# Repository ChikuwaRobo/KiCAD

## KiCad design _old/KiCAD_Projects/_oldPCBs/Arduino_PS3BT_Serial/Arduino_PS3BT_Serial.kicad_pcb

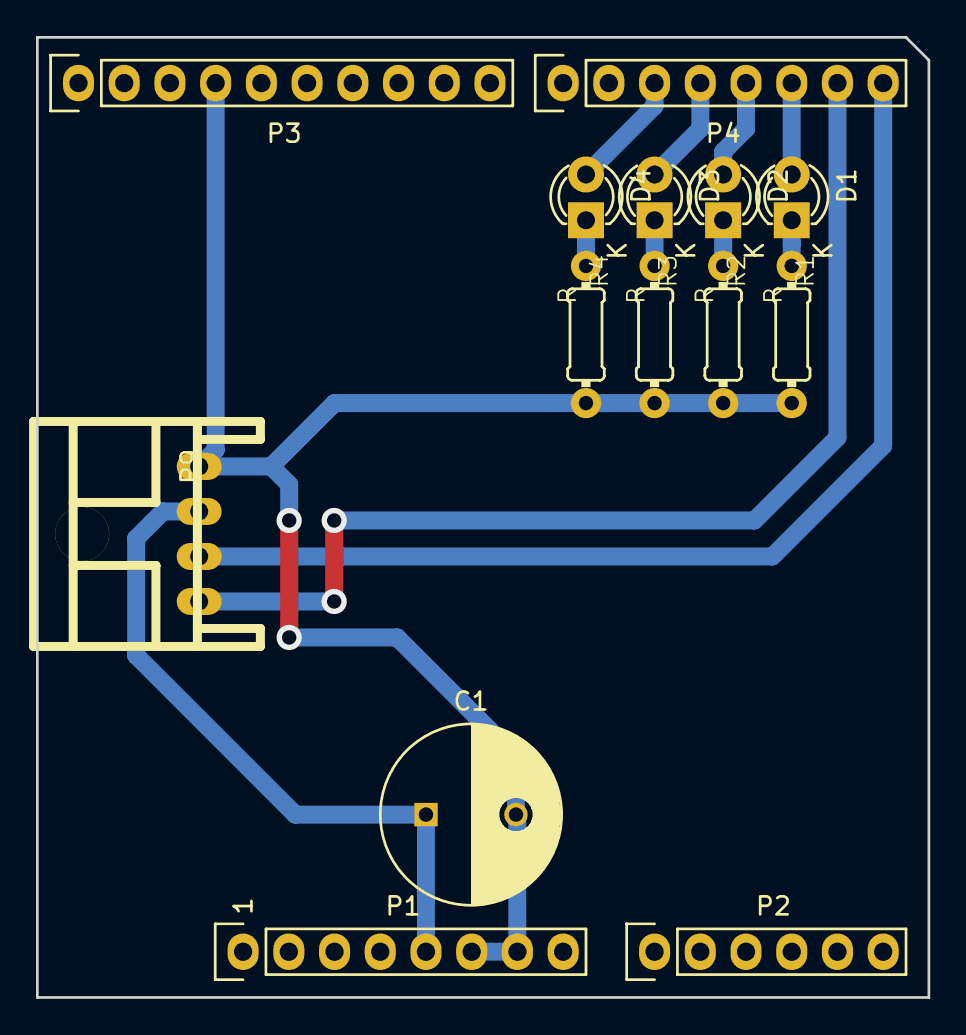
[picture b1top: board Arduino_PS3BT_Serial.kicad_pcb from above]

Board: 2 copper layers, 49.5 x 53.3 mm, 14 parts (0 on the bottom side), 14 nets.

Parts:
C1: 100u; C_Radial_D10_L20_P5
D1, D2, D3, D4: LED; LED-3MM
P1: Power; Socket_Strip_Arduino_1x08
P2: Analog; Socket_Strip_Arduino_1x06
P3: Digital; Socket_Strip_Arduino_1x10
P4: Digital; Socket_Strip_Arduino_1x08
P9: CONN_01X04; XA_4LC
R1, R2, R3, R4: R; 0204_2f7

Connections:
+5V: C1.1, P1.5, P9.2
/0(Rx): P4.8, P9.3
/1(Tx): P4.7, P9.4
/2: D1.2, P4.6
/3(**): D2.2, P4.5
/4: D3.2, P4.4
/5(**): D4.2, P4.3
/A4(SDA): P2.5, P3.2
/A5(SCL): P2.6, P3.1
GND: C1.2, P1.6, P1.7, P3.4, P9.1, R1.2, R2.2, R3.2, R4.2
unnamed: D1.1, R1.1
unnamed: D2.1, R2.1
unnamed: D3.1, R3.1
unnamed: D4.1, R4.1

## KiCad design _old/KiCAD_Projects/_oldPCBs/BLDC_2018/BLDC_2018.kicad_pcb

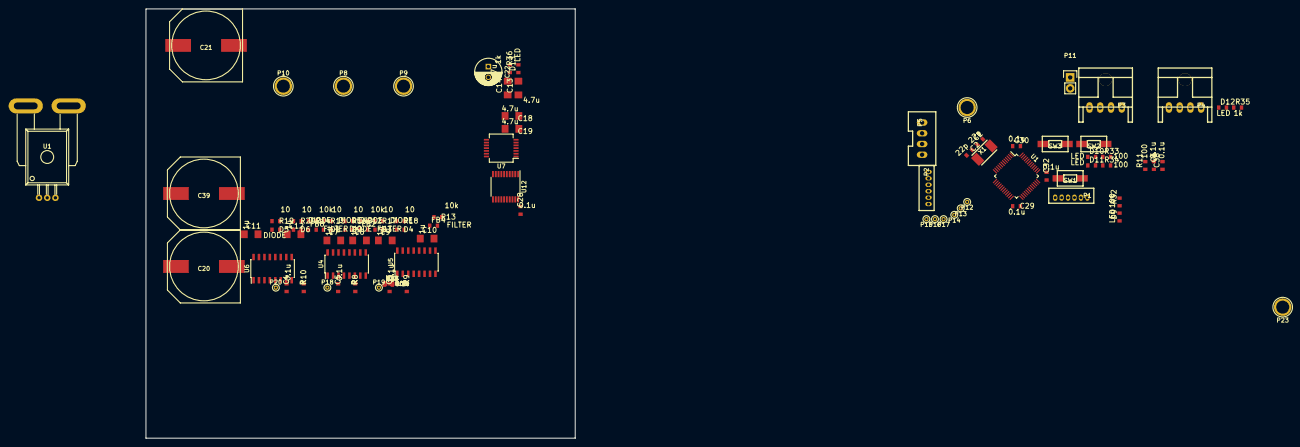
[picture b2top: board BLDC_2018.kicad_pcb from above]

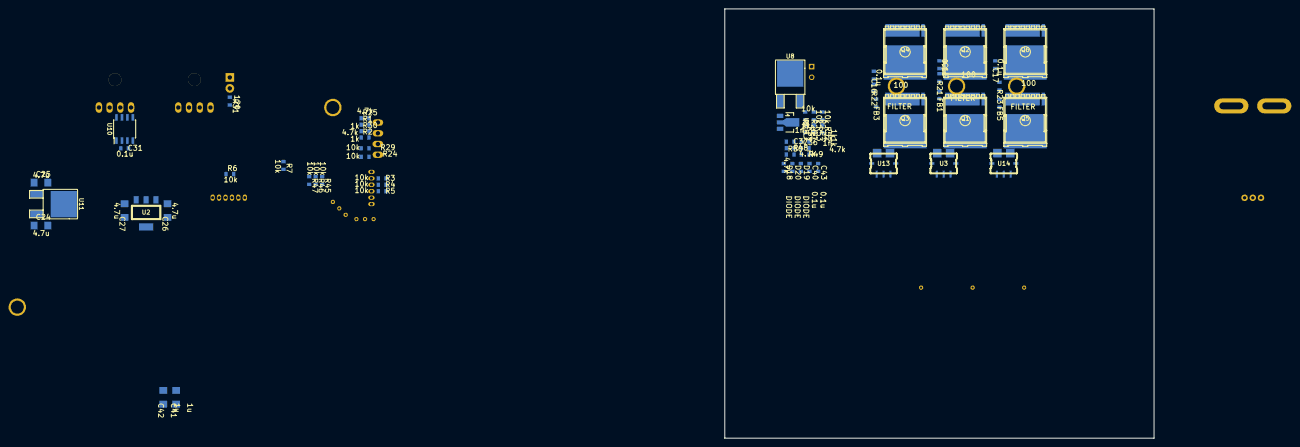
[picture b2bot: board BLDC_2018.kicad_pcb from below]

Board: 2 copper layers, 100.0 x 100.0 mm, 157 parts (62 on the bottom side), 97 nets, no tracks yet.

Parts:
C1, C2: 22p; C1608_WP
C3, C4, C5, C6, C15, C16, C17, C23, C28, C29, C30, C31, C32, C33, C34, C38, C40, C43, C44, C45: 0.1u; C1608_WP
C7, C8, C9, C10, C11, C12, C41, C42: 1u; C3216
C13, C14, C18, C19, C24, C25, C26, C27: 4.7u; C3216
C20, C21, C39: 470u; c_elec_16x17
C22: 100u; C_Radial_D6.3_L11.2_P2.5
C35, C36, C37: 1n; C1608_WP
D1, D2, D3, D4, D5, D6, D18, D19, D20: DIODE; C1608_WP
D9, D10, D11, D12, D13: LED; C1608_WP
FB1, FB2, FB3, FB4, FB5, FB6: FILTER; C1608_WP
P1, P2: CONN_01X06; ZH_6T
P3, P4: CONN_01X04; XA_4LC
P5: CONN_01X04; XA_4T
P6, P8, P9, P10, P23: CONN_01X01; 1pin
P11: CONN_01X02; Pin_Header_Straight_1x02
P12, P13, P14, P15, P16, P17, P18, P19, P20: CONN_01X01; PINTST
Q1, Q2, Q3, Q4, Q5, Q6: MOSFET_N; HSOF-8-1
R1, R2, R35, R36, R52, R53, R54: 1k; C1608_WP
R3, R4, R5, R6, R7, R12, R13, R14, R24, R26, R27, R28, R29, R45, R46, R47: 10k; C1608_WP
R8, R9, R10: R; C1608_WP
R11, R21, R22, R23, R32, R33, R34, R37, R38: 100; C1608_WP
R15, R16, R17, R18, R19, R20: 10; C1608_WP
R25, R30, R48, R49, R50: 4.7k; C1608_WP
R31: 120; C1608_WP
SW1, SW2, SW3: SW_PUSH; RP_SMD_Button
U1: STM32F103_48; LQFP-48_7x7mm_Pitch0.5mm
U1#2: ACS758; ACS785xCB
U2: NCP1117ST33T3G; SOT-223_reg
U3, U13, U14: ACS758; ACS78x
U4, U5, U6: SI8234; SOIC-16_3.9x9.9mm_Pitch1.27mm
U7: LM324; SSOP-14_5.3x6.2mm_Pitch0.65mm
U8: LM7812ACT; TO-252-2Lead
U9: LM7805CT; SOT89-3_Housing
U10: MAX3051; SOIC-8_3.9x4.9mm_Pitch1.27mm
U11: LM7805CT; TO-252-2Lead
U12: ADUM7640; TSSOP-20_4.4x6.5mm_Pitch0.65mm
X1: CRYSTAL; ABM3_2pads

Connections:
+3.3V: C3.1, C4.1, C5.1, C6.1, C23.1, C26.1, C28.1, C29.1, C30.1, C31.1, C32.1, C33.1, C38.1, D9.1, P1.2, R6.1, U1.1, U1.9, U1.24, U1.36, U1.48, U2.2, U4.3, U4.8, U5.3, U5.8, U6.3, U6.8, U10.3, U12.14, U12.20
+5V: C24.1, C27.1, P2.6, P5.2, R1.1, R2.1, R3.1, R4.1, R5.1, U2.3, U11.3
+12V: C25.1, D12.1, P3.2, P4.2, U11.1
+BATT: C15.1, C16.2, C17.2, C20.1, C21.1, C39.1, C41.1, C42.1, P6.1, U3.5, U7.4, U13.5, U14.5
/BOOT0: R7.1, U1.44
/CAN_H: P3.3, P4.3, R31.2, U10.7
/CAN_L: P3.4, P4.4, P11.1, U10.6
/CAN_RX: U1.32, U10.4
/CAN_TX: U1.33, U10.1
/COMP_U: P15.1, U1.16, U12.18
/COMP_V: P16.1, U1.17, U12.17
/COMP_W: P17.1, U1.18, U12.16
/ENC_A: P5.3, R2.2, R30.2
/ENC_B: P5.4, R1.2, R25.2
/EN_U: R47.2, U1.15, U6.5
/EN_V: R46.2, U1.14, U4.5
/EN_W: R45.2, U1.13, U5.5
/GD_12V: C14.1, C18.1, D13.1, R15.1, R16.1, R17.1, R18.1, R19.1, R20.1, U8.3, U9.1
/HALL_0: P2.2, P12.1, R3.2, U1.19
/HALL_1: P2.3, P13.1, R4.2, U1.20
/HALL_2: P2.4, P14.1, R5.2, U1.21
/I_SENSE_U: C34.2, C44.2, C45.2, R11.2, R37.2, R38.2
/LED_A: D10.1, U1.42
/LED_B: D11.1, U1.41
/NRST: R6.2, SW1.2, U1.7
/OUT_CENTER: C35.1, C36.1, C37.1, C40.1, R26.2, R27.2, R28.2, U7.2, U7.9, U7.13
/OUT_U: C11.2, P10.1, Q5.S, Q6.D, R23.1, R28.1, R54.1, U6.14
/OUT_V: C7.2, P8.1, Q1.S, Q2.D, R21.1, R26.1, R53.1, U4.14
/OUT_W: C9.2, P9.1, Q3.S, Q4.D, R22.1, R27.1, R52.1, U5.14
/PWM_U: P20.1, U1.28, U6.1
/PWM_V: P18.1, U1.27, U4.1
/PWM_W: P19.1, U1.26, U5.1
/PW_5V: C19.1, C43.1, D18.1, D19.1, D20.1, U9.3, U12.1, U12.7
/PW_PW: C13.1, C22.1, U8.1
/SW1: SW2.2, U1.45
/SW2: SW3.2, U1.46
/SWCLK: P1.3, U1.37
/SWDIO: P1.4, U1.34
/USART_RX: P1.6, U1.31
/USART_TX: P1.5, U1.30
GND: C1.1, C2.1, C3.2, C4.2, C5.2, C6.2, C23.2, C24.2, C25.2, C26.2, C27.2, C28.2, C29.2, C30.2, C31.2, C32.2, C33.2, C34.1, C38.2, C44.1, C45.1, P1.1, P2.1, P3.1, P4.1, P5.1, R7.2, R8.2, R9.2, R10.2, R24.1, R29.1, R32.2, R33.2, R34.2, R35.2, R45.1, R46.1, R47.1, SW1.1, SW2.1, SW3.1, U1.8, U1.23, U1.35, U1.47, U2.1, U4.4, U5.4, U6.4, U10.2, U10.5, U10.8, U11.2, U12.11, U12.19
GNDPWR: C8.2, C10.2, C12.2, C13.2, C14.2, C18.2, C19.2, C20.2, C21.2, C22.2, C39.2, C40.2, C41.2, C42.2, C43.2, P23.1, Q2.S, Q4.S, Q6.S, R12.1, R13.1, R14.1, R36.2, U4.9, U5.9, U6.9, U7.11, U8.2, U9.2, U12.2, U12.10
unnamed: C1.2, U1.5, X1.1
unnamed: C2.2, U1.6, X1.2
unnamed: C7.1, D1.1, U4.16
unnamed: C8.1, D2.1, U4.11
unnamed: C9.1, D3.1, U5.16
unnamed: C10.1, D4.1, U5.11
unnamed: C11.1, D5.1, U6.16
unnamed: C12.1, D6.1, U6.11
unnamed: C15.2, R21.2
unnamed: C16.1, R22.2
unnamed: C17.1, R23.2
unnamed: C35.2, R54.2, U7.10
unnamed: C36.2, R52.2, U7.12
unnamed: C37.2, R53.2, U7.3
unnamed: D1.2, R15.2
unnamed: D2.2, R16.2
unnamed: D3.2, R17.2
unnamed: D4.2, R18.2
unnamed: D5.2, R19.2
unnamed: D6.2, R20.2
unnamed: D9.2, R32.1
unnamed: D10.2, R33.1
unnamed: D11.2, R34.1
unnamed: D12.2, R35.1
unnamed: D13.2, R36.1
unnamed: D18.2, R48.2, U12.3
unnamed: D19.2, R49.2, U12.5
unnamed: D20.2, R50.2, U12.4
unnamed: FB1.1, U4.15
unnamed: FB1.2, Q1.G
unnamed: FB2.1, R12.2, U4.10
unnamed: FB2.2, Q2.G
unnamed: FB3.1, U5.15
unnamed: FB3.2, Q3.G
unnamed: FB4.1, R13.2, U5.10
unnamed: FB4.2, Q4.G
unnamed: FB5.1, U6.15
unnamed: FB5.2, Q5.G
unnamed: FB6.1, R14.2, U6.10
unnamed: FB6.2, Q6.G
unnamed: P11.2, R31.1
unnamed: Q1.D, U3.4
unnamed: Q3.D, U13.4
unnamed: Q5.D, U14.4
unnamed: R8.1, U4.6
unnamed: R9.1, U5.6
unnamed: R10.1, U6.6
unnamed: R11.1, U3.3
unnamed: R24.2, R25.1, U1.11
unnamed: R29.2, R30.1, U1.10
unnamed: R37.1, U13.3
unnamed: R38.1, U14.3
unnamed: R48.1, U7.8
unnamed: R49.1, U7.14
unnamed: R50.1, U7.1

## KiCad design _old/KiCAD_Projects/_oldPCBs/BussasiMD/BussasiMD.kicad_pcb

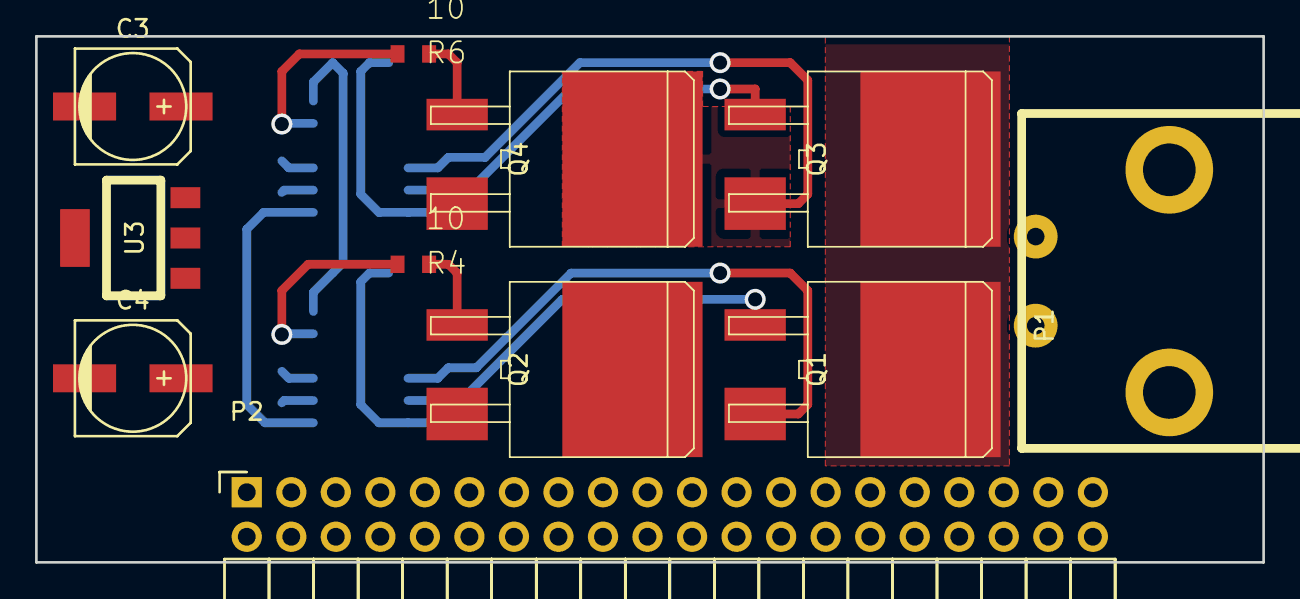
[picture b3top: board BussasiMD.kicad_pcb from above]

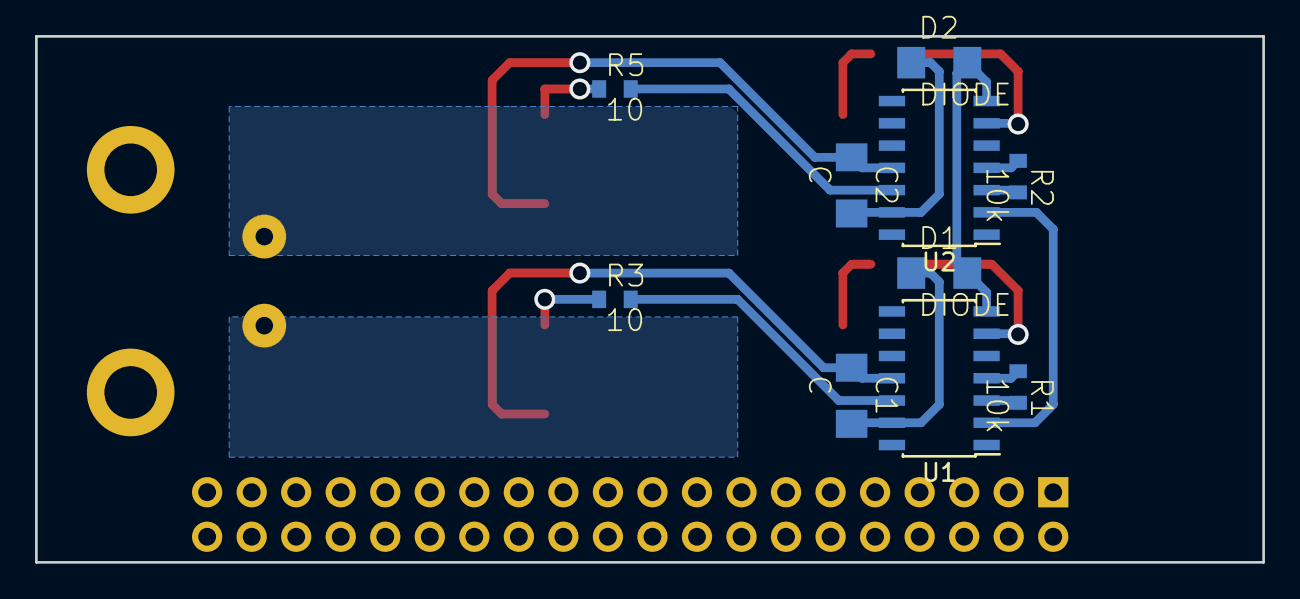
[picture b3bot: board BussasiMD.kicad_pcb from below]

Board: 2 copper layers, 70.0 x 30.0 mm, 21 parts (10 on the bottom side), 21 nets.

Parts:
C1, C2: C; C3216
C3, C4: 100u; c_elec_6.3x4.5
D1, D2: DIODE; C3216
P1: CONN_01X02; D-3200S_2L
P2: CONN_02X20; Socket_Strip_Angled_2x20
Q1, Q2, Q3, Q4: MOSFET_N; D2-PAK_compact
R1, R2: 10k; C1608_WP
R3, R4, R5, R6: 10; C1608_WP
U1, U2: FAN7393; SOIC-14_3.9x8.7mm_Pitch1.27mm
U3: LM7812ACT; SOT-223_reg

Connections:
+12V: C4.1, D1.2, D2.2, U1.7, U2.7, U3.3
+BATT: C3.1, P2.23, P2.24, P2.25, P2.26, P2.27, P2.28, P2.29, P2.30, P2.31, P2.32, P2.33, P2.34, P2.35, P2.36, P2.37, P2.38, P2.39, P2.40, Q1.D, Q3.D, U3.1
/EN: P2.3, U1.2, U2.2
/OUT_A: C1.1, P1.1, Q1.S, Q2.D, U1.11
/OUT_B: C2.1, P1.2, Q3.S, Q4.D, U2.11
/PWM_A: P2.4, U1.1
/PWM_B: P2.2, U2.1
GND: C3.2, C4.2, P2.1, R1.2, R2.2, U1.3, U2.3, U3.2
GNDPWR: P2.5, P2.6, P2.7, P2.8, P2.9, P2.10, P2.11, P2.12, P2.13, P2.14, P2.15, P2.16, P2.17, P2.18, P2.19, P2.20, P2.21, P2.22, Q2.S, Q4.S, U1.5, U2.5
unnamed: C1.2, D1.1, U1.13
unnamed: C2.2, D2.1, U2.13
unnamed: Q1.G, R3.1
unnamed: Q2.G, R4.1
unnamed: Q3.G, R5.1
unnamed: Q4.G, R6.1
unnamed: R1.1, U1.4
unnamed: R2.1, U2.4
unnamed: R3.2, U1.12
unnamed: R4.2, U1.6
unnamed: R5.2, U2.12
unnamed: R6.2, U2.6

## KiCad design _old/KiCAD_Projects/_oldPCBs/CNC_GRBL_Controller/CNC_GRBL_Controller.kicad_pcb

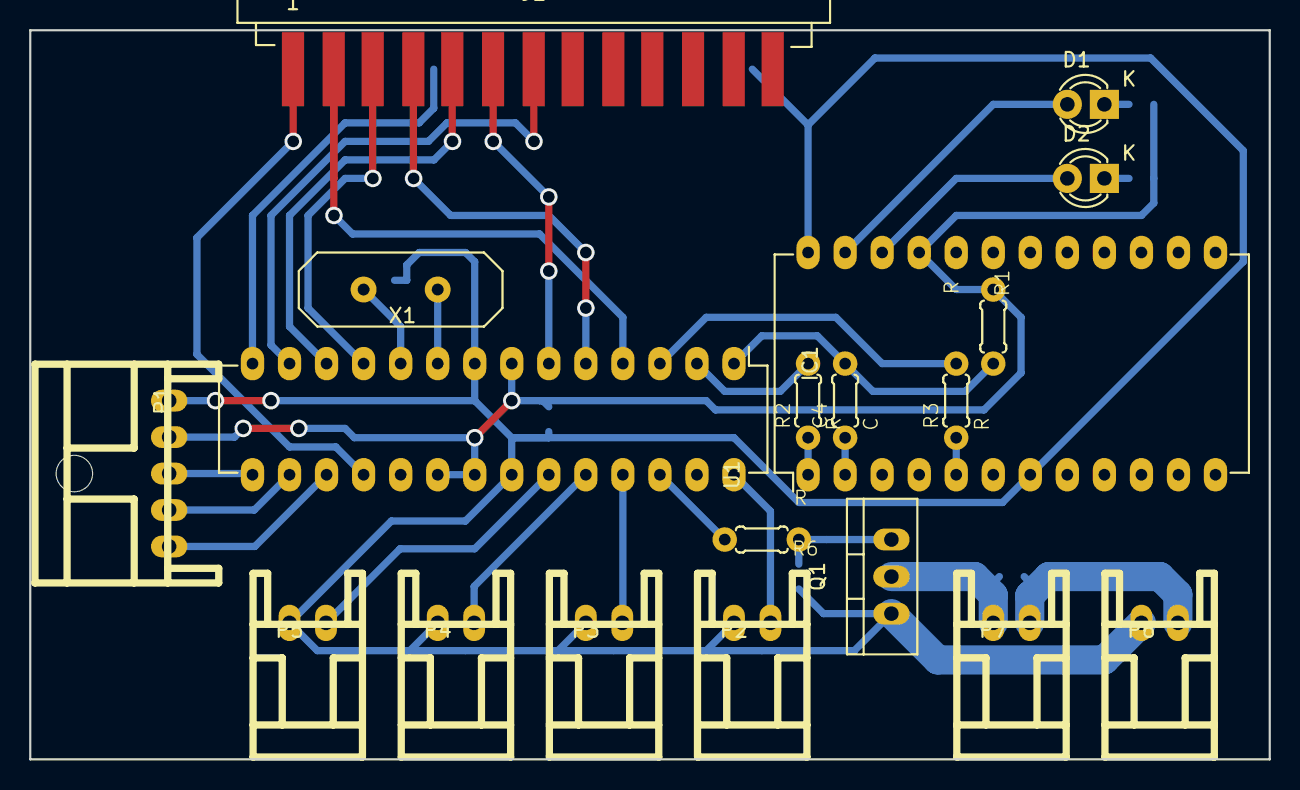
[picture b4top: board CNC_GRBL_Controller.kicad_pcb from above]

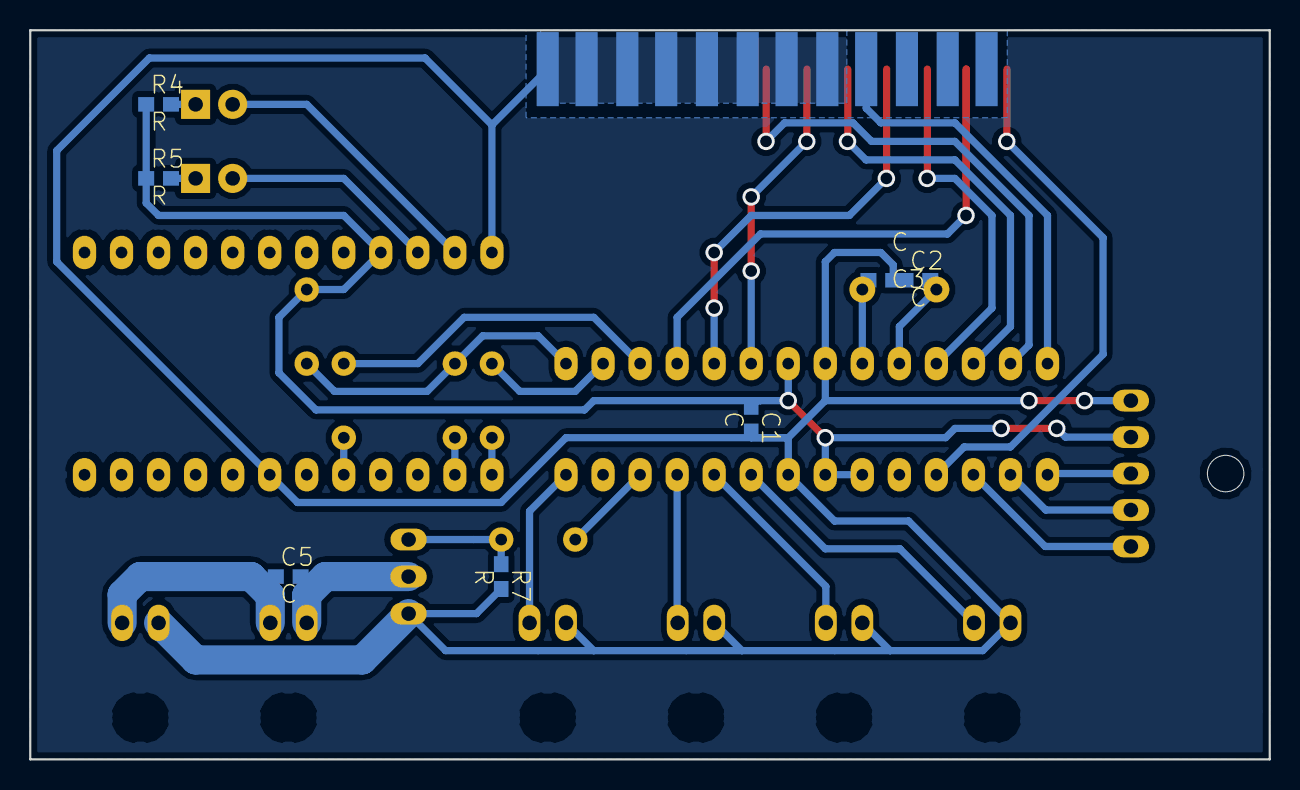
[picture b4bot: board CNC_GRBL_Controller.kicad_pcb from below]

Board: 2 copper layers, 85.0 x 50.0 mm, 26 parts (7 on the bottom side), 33 nets.

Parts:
C1, C2, C3, C5: C; C1608
C4: C; 0204_2f5
D1, D2: LED; LED-3MM
IC1: ATMEGA328-P; DIP-28_W7.62mm_LongPads
J1: DB25; DB25F_CI
P1: CONN_01X05; XA_5L
P2, P3, P4, P5, P6, P7: CONN_01X02; XA_2L
Q1: MOSFET_N; TO-220_Neutral123_Vertical
R1, R2, R3, R6: R; 0204_2f5
R4, R5, R7: R; C1608
U1: AE-UM232R; DIP-24_W15.24mm_LongPads
X1: CRYSTAL; HC-18UV

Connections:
+5V: C1.1, IC1.7, IC1.20, IC1.21, P1.2, R1.1, R4.1, R5.1, U1.21
+12V: C5.1, P6.2, P7.2
/Arduino_RESET: C4.2, IC1.1, R1.2
/Arduino_RX: IC1.2, R2.2
/Arduino_TX: IC1.3, R3.2
/Coolant_EN: IC1.26, R6.2
/Cycle_Stat: IC1.25, P3.2
/Feed_Hold: IC1.24, P4.2
/Limit_X: IC1.15, P1.3
/Limit_Y: IC1.16, P1.4
/Limit_Z: IC1.17, P1.5
/Probe: IC1.28, P2.2
/Reset/Abort: IC1.23, P5.2
/Spindle_EN: IC1.18, J1.1
/Stepper_~EN: IC1.14, J1.17
/X_Dir: IC1.11, J1.3
/X_Step: IC1.4, J1.2
/Y_Dir: IC1.12, J1.5
/Y_Step: IC1.5, J1.4
/Z_Dir: IC1.13, J1.7
/Z_Step: IC1.6, J1.6
GND: C1.2, C2.1, C3.1, IC1.8, IC1.22, J1.18, J1.19, J1.20, J1.21, J1.22, J1.23, J1.24, J1.25, P1.1, P2.1, P3.1, P4.1, P5.1, P6.1, Q1.S, R7.2, U1.7, U1.24
unnamed: C2.2, IC1.10, X1.2
unnamed: C3.2, IC1.9, X1.1
unnamed: C4.1, U1.2
unnamed: C5.2, P7.1, Q1.D
unnamed: D1.1, R4.2
unnamed: D1.2, U1.23
unnamed: D2.1, R5.2
unnamed: D2.2, U1.22
unnamed: Q1.G, R6.1, R7.1
unnamed: R2.1, U1.1
unnamed: R3.1, U1.5

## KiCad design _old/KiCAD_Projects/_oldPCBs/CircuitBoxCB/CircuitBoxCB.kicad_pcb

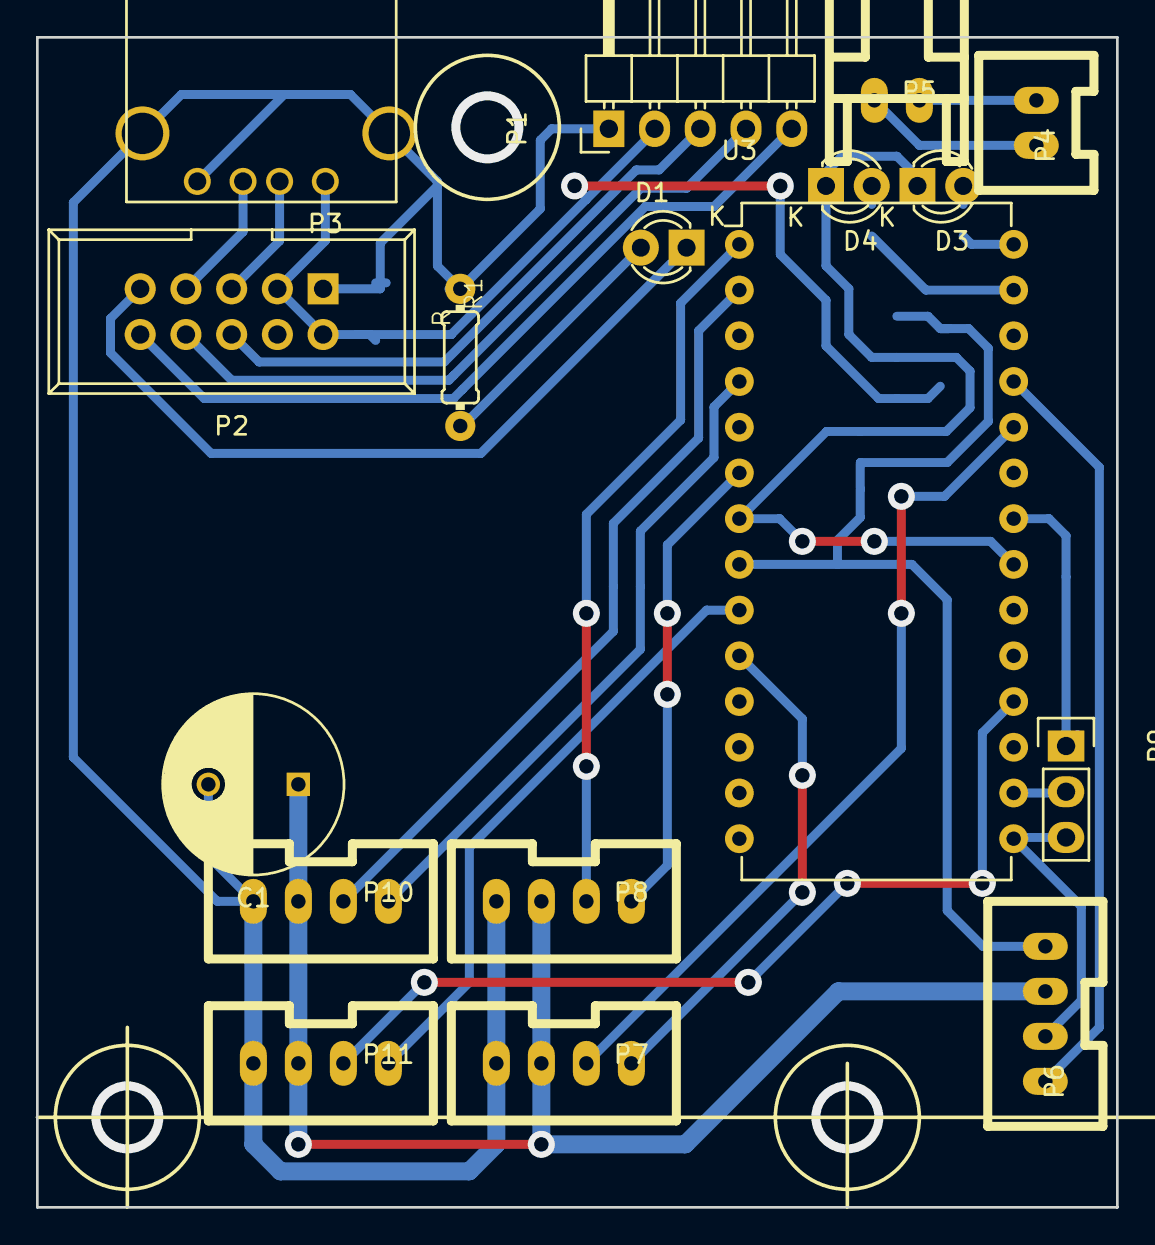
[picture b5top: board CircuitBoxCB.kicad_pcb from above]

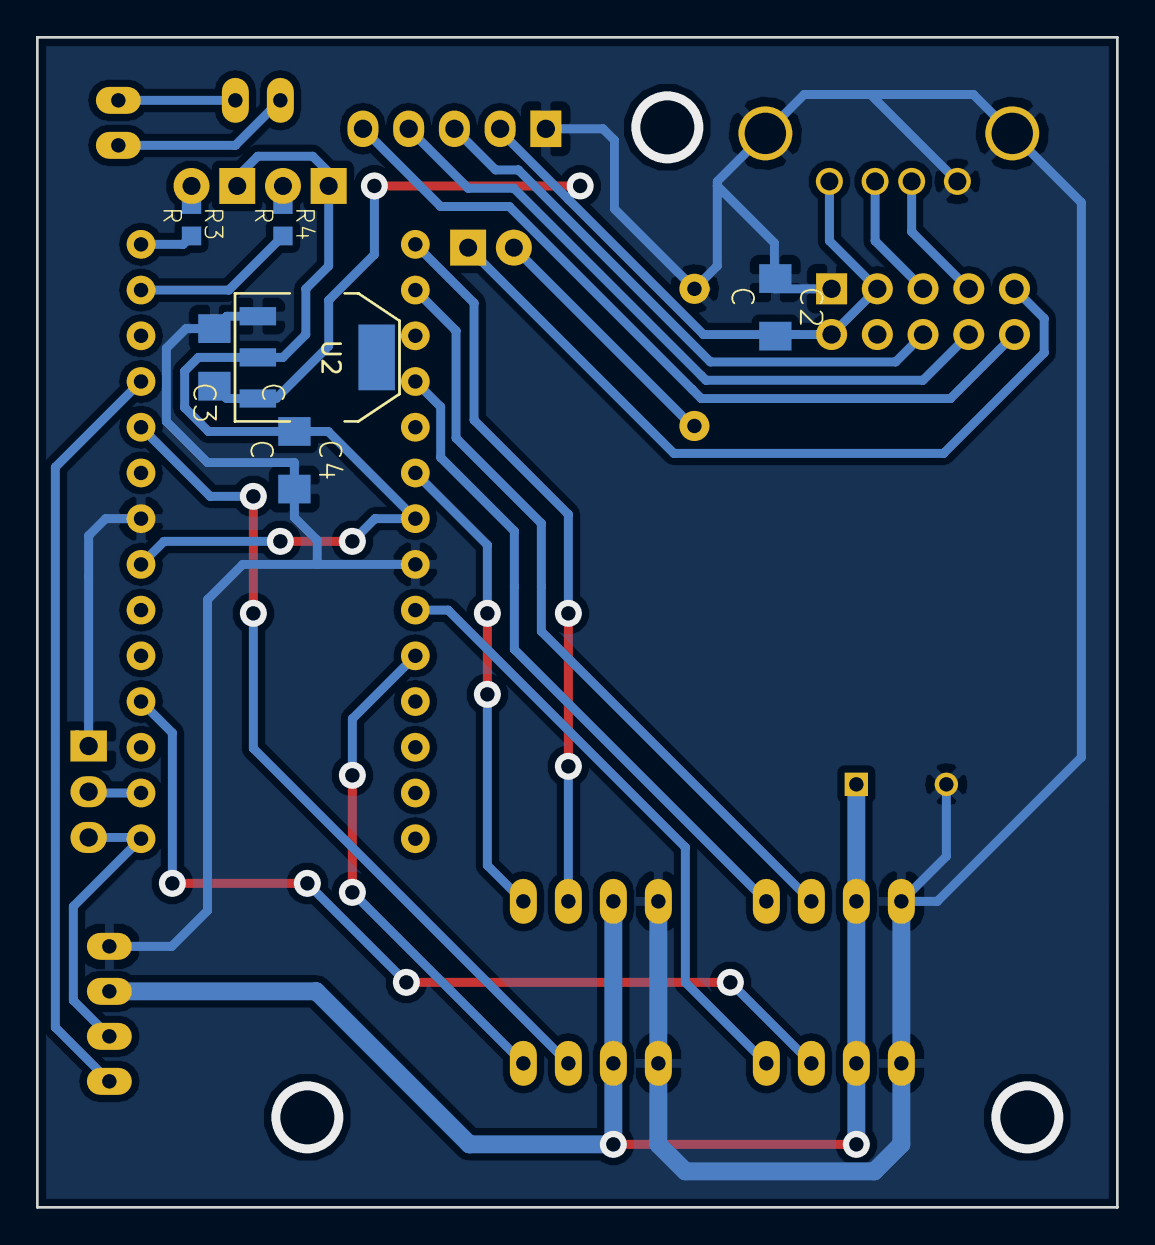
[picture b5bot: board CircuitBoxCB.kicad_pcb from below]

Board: 2 copper layers, 60.0 x 65.0 mm, 23 parts (6 on the bottom side), 28 nets.

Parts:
C1: C; C_Radial_D10_L13_P5
C2, C3, C4: C; C3216
D1, D3, D4: LED; LED-3MM
P1: CONN_01X05; Pin_Header_Angled_1x05
P2: CONN_02X05; IDC_Header_Straight_10pins
P3: USB_A
P4: CONN_01X02; XA_2T
P5: CONN_01X02; XA_2S
P6, P7, P8, P10, P11: CONN_01X04; XA_4T
P9: CONN_01X03; Socket_Strip_Straight_1x03
R1: R; 0204_2f7
R3, R4: R; C0603K
U2: LM1084IT-3.3/NOPB; SOT-223
U3: LPC1114FN28; DIP-28_W15.24mm

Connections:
5V_reray: C1.1, P6.2, P7.2, P8.2, P10.2, P11.2
1114_RX: P6.3, P9.3, U3.15
1114_TX: P9.2, U3.16
+3.3V: C4.1, D3.1, D4.1, U2.2, U3.7, U3.21
+5V: C2.2, C3.1, P1.2, P2.2, P2.3, P3.1, U2.3
EN: P6.4, U3.25
GND: C1.2, C2.1, C3.2, C4.2, P1.1, P2.1, P3.4, P3.5, P6.1, P7.1, P8.1, P9.1, P10.1, P11.1, R1.1, U2.1, U3.8, U3.22
LED_1: R4.2, U3.27
LED_2: R3.2, U3.28
unnamed: D1.1, P2.9
unnamed: D1.2, R1.2
unnamed: D3.2, R3.1
unnamed: D4.2, R4.1
unnamed: P1.3, P2.6
unnamed: P1.4, P2.8
unnamed: P1.5, P2.10
unnamed: P2.5, P3.2
unnamed: P2.7, P3.3
unnamed: P4.1, P5.1
unnamed: P4.2, P5.2
PWM_0: P8.3, U3.1
PWM_1: P10.3, U3.2
PWM_2: P11.3, U3.18
PWM_3: P7.3, U3.24
SIGN_0: P8.4, U3.6
SIGN_1: P10.4, U3.4
SIGN_2: P11.4, U3.9
SIGN_3: P7.4, U3.10

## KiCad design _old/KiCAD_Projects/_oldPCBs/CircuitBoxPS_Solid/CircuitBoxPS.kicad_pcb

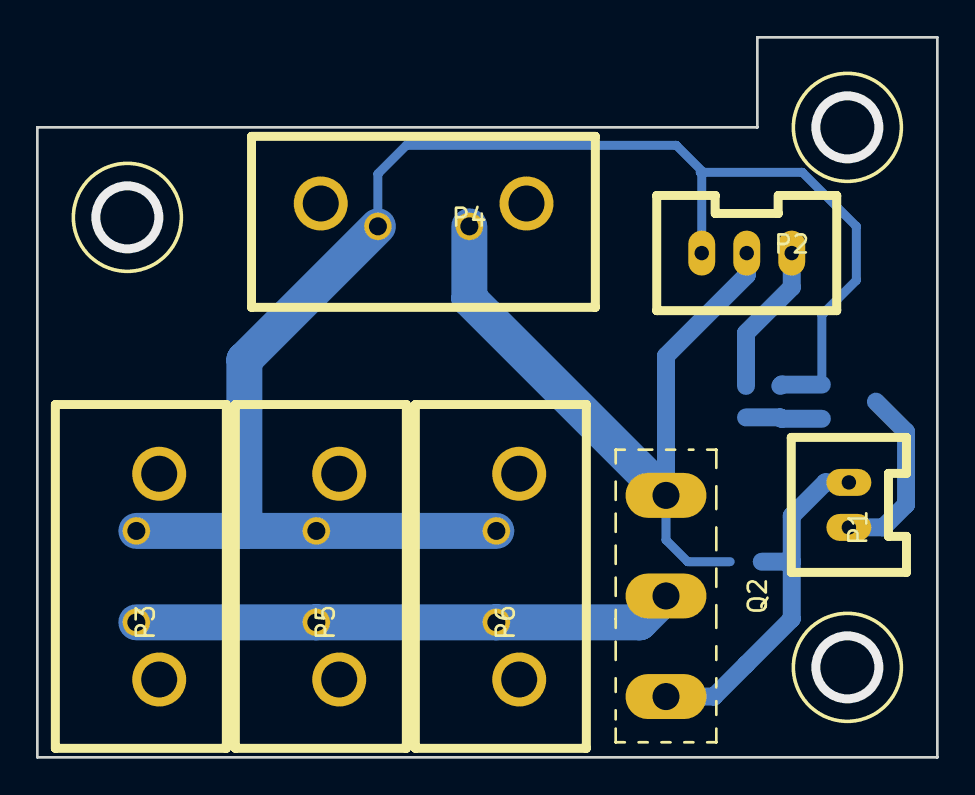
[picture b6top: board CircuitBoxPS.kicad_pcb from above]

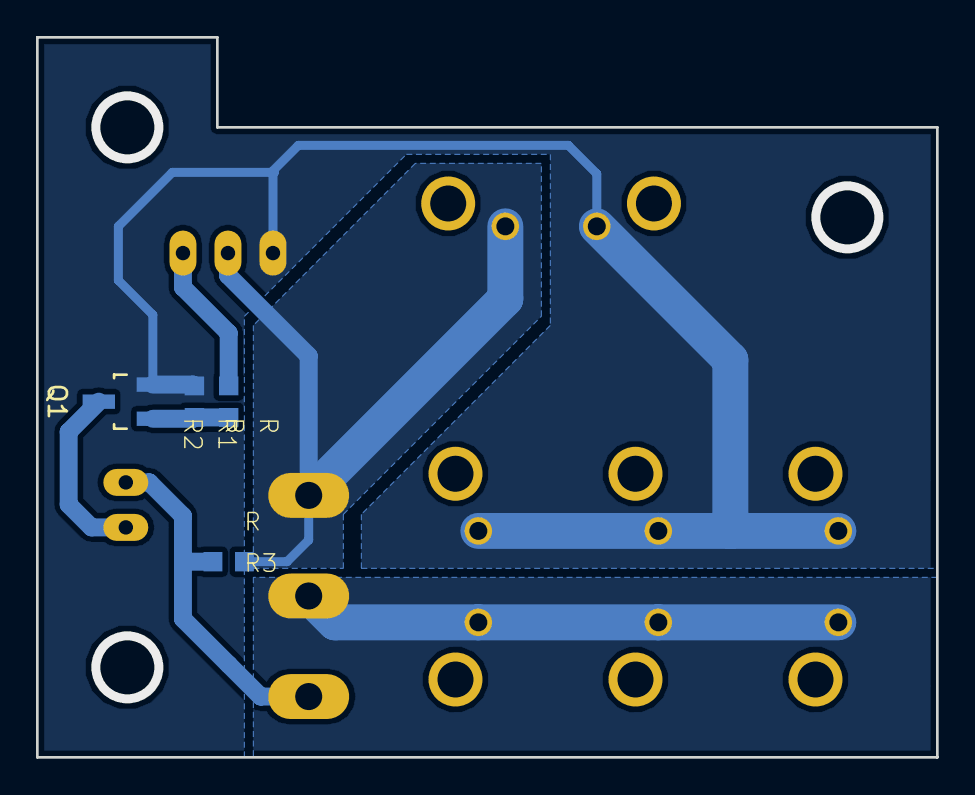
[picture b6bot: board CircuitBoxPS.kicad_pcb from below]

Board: 2 copper layers, 50.0 x 40.0 mm, 11 parts (4 on the bottom side), 7 nets.

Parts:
P1: CONN_01X02; XA_2T
P2: CONN_01X03; XA_3T
P3, P4, P5, P6: CONN_01X02; D3200_2T
Q1: MOSFET_N; SOT-23_Handsoldering
Q2: FET_P; TO-247_Vertical_Neutral123_MountedFromLS
R1, R2, R3: R; C0603K

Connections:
+BATT: P2.2, P4.2, Q2.S, R3.1
/OUT: P3.2, P5.2, P6.2, Q2.D
GNDPWR: P2.1, P3.1, P4.1, P5.1, P6.1, Q1.S, R2.2
unnamed: P1.1, Q2.G, R3.2
unnamed: P1.2, Q1.D
unnamed: P2.3, R1.2
unnamed: Q1.G, R1.1, R2.1
